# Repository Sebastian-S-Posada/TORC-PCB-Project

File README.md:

# TORC-PCB-Project
This is a repository for my senior design project

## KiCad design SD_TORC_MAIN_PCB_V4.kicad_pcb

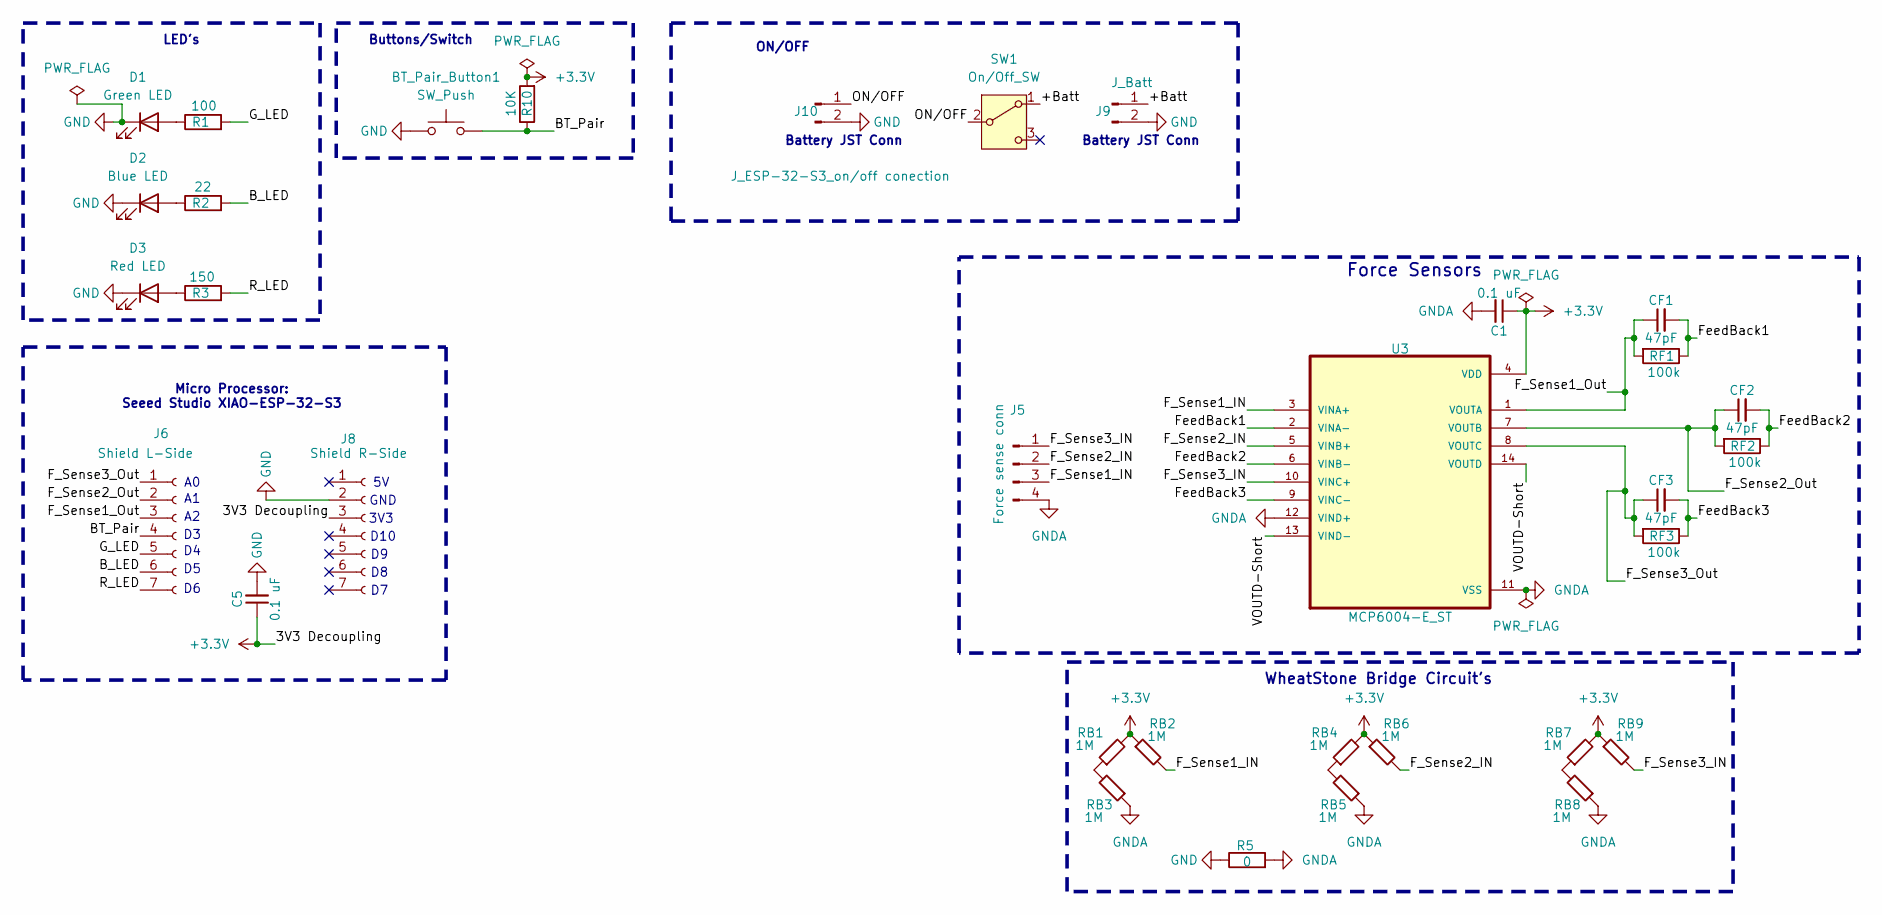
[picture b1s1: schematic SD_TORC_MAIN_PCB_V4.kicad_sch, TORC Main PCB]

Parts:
BT_Pair_Button1: SW_Push; SW_SPST_CK_KMS2xxGP; Mfr # KMR221G LFS; Digikey # 108-KMR221GLFSDKR-ND
C1, C5: 0.1 uF; C_0603_1608Metric_Pad1.08x0.95mm_HandSolder; Mouser # 581-0603ZG104ZAT2A
CF1, CF2, CF3: 47pF; C_0603_1608Metric_Pad1.08x0.95mm_HandSolder; Mouser # 581-06035U470GAT2A
D1: Green LED; LED_0805_2012Metric_Pad1.15x1.40mm_HandSolder; Mouser # 720-Q62702P5179
D2: Blue LED; LED_0805_2012Metric_Pad1.15x1.40mm_HandSolder; Mouser # 645-599-0190-137F
D3: Red LED; LED_0805_2012Metric_Pad1.15x1.40mm_HandSolder; Mouser # 720-Q62702P5178
J5: Force sense conn; JST_XH_B4B-XH-AM_1x04_P2.50mm_Vertical; Mfr# B4B-XH-AM; DigiKey# 455-B4B-XH-AM-ND
J6: Shield L-Side; PinSocket_1x07_P2.54mm_Vertical
J8: Shield R-Side; PinSocket_1x07_P2.54mm_Vertical
J9: J_Batt; JST_PH_B2B-PH-K_1x02_P2.00mm_Vertical; Mfr# S2B-PH-K-S; DigiKey # 455-1719-ND
J10: J_ESP-32-S3_on/off conection; JST_PH_B2B-PH-K_1x02_P2.00mm_Vertical; Mfr# S2B-PH-K-S; DigiKey # 455-1719-ND
R1: 100; R_0603_1608Metric_Pad0.98x0.95mm_HandSolder; Mouser # 710-560112116009
R2: 22; R_0603_1608Metric_Pad0.98x0.95mm_HandSolder; Mouser # 710-560112116043
R3: 150; R_0603_1608Metric_Pad0.98x0.95mm_HandSolder; Mouser # 710-560112116041
R5: 0; R_0603_1608Metric_Pad0.98x0.95mm_HandSolder; Mouser # 708-MCJ0603ZT0R00
R10: 10K; R_0603_1608Metric_Pad0.98x0.95mm_HandSolder; Mouser # 279-RQ73C1J10KBTD
RB1, RB2, RB3, RB4, RB5, RB6, RB7, RB8, RB9: 1M; R_0603_1608Metric_Pad0.98x0.95mm_HandSolder; Mouser # 652-CMP0603AFX-1004L
RF1, RF2, RF3: 100k; R_0603_1608Metric_Pad0.98x0.95mm_HandSolder; Mouser # 871-B57355V5104F360
SW1: On/Off_SW; SW_Slide_SPDT_Straight_CK_OS102011MS2Q; Mfr # OS102011MS2QN1; Digikey # CKN9565-ND
U3: MCP6004-E_ST; SOP65P640X120-14N; Mouser # 579-MCP6004-E/ST

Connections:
+3.3V: C1.1, C5.1, J8.3, R10.2, RB1.2, RB2.1, RB4.2, RB6.1, RB7.2, RB9.1, U3.4 (VDD)
/+Batt: J9.1, SW1.1 (A)
/BT_Pair: BT_Pair_Button1.2, J6.4, R10.1; also elsewhere on the board
/B_LED: J6.6, R2.2
/F_Sense1_IN: J5.3, RB2.2, U3.3 (VINA+)
/F_Sense1_Out: CF1.1, J6.3, RF1.2, U3.1 (VOUTA)
/F_Sense2_IN: J5.2, RB6.2, U3.5 (VINB+)
/F_Sense2_Out: CF2.1, J6.2, RF2.2, U3.7 (VOUTB)
/F_Sense3_IN: J5.1, RB9.2, U3.10 (VINC+)
/F_Sense3_Out: CF3.1, J6.1, RF3.2, U3.8 (VOUTC)
/FeedBack1: CF1.2, RF1.1, U3.2 (VINA-)
/FeedBack2: CF2.2, RF2.1, U3.6 (VINB-)
/FeedBack3: CF3.2, RF3.1, U3.9 (VINC-)
/G_LED: J6.5, R1.2
/ON/OFF: J10.1, SW1.2 (B)
/R_LED: J6.7, R3.2
/VOUTD-Short: U3.13 (VIND-), U3.14 (VOUTD)
GND: BT_Pair_Button1.1, C5.2, D1.1 (K), D2.1 (K), D3.1 (K), J8.2, J9.2, J10.2, R5.1; also elsewhere on the board
GNDA: C1.2, J5.4, R5.2, RB3.1, RB5.1, RB8.1, U3.11 (VSS), U3.12 (VIND+)
unnamed: D1.2 (A), R1.1
unnamed: D2.2 (A), R2.1
unnamed: D3.2 (A), R3.1
unnamed: RB1.1, RB3.2
unnamed: RB4.1, RB5.2
unnamed: RB7.1, RB8.2

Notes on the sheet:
WheatStone Bridge Circuit's
GND
Micro Processor: Seeed Studio XIAO-ESP-32-S3
Battery JST Conn
3V3
ON/OFF
D10
Buttons/Switch
Force Sensors
LED's

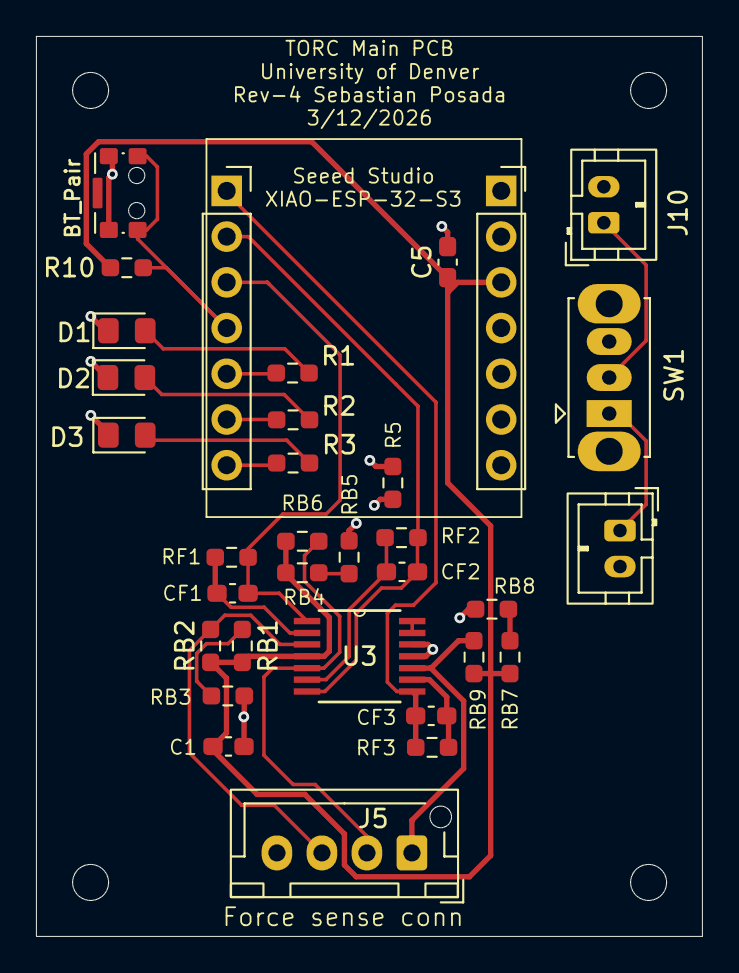
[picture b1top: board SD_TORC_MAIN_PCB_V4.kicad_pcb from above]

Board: 2 copper layers, 37.0 x 50.0 mm, 33 parts (0 on the bottom side), 25 nets.

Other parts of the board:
BT_Pair: SW_Push; SW_SPST_CK_KMS2xxGP

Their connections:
/BT_Pair: BT_Pair.2; also elsewhere on the board
GND: BT_Pair.1; also elsewhere on the board

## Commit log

2026-03-13 Add files via upload
    Upload KiCad project files
